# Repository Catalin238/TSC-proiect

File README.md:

# TSC-proiect

1. Diagrama Bloc

2. Bill of materials

| Piece Name | Quantity | Link |
|------------|----------|------|
| ESP32 | 1 | https://www.snapeda.com/parts/ESP32-C6-WROOM-1-N8/Espressif%20Systems/view-part/?ref=search&t=ESP32-C6-WROOM-1-N8 |
| BME680 | 1 | https://www.snapeda.com/parts/BME680/Bosch%20Sensortec/view-part/?ref=search&t=bme680 |
| DS3231SN | 1 | https://www.snapeda.com/parts/DS3231SN%23/Analog%20Devices/view-part/?ref=search&t=DS3231SN%23 |
| W25Q512JVEIQ | 1 | https://www.snapeda.com/parts/W25Q512JVEIQ/Winbond%20Electronics/view-part/?ref=search&t=W25Q512JVEIQ |
| MCP73831 | 1 | https://componentsearchengine.com/part-view/MCP73831T-2ACI%2FOT/Microchip |
| MOSFET | 1 | https://componentsearchengine.com/part-view/DMG2305UX-7/Diodes%20Incorporated |
| SAMACSYS_PARTS_USB4110-GF-A | 1 | https://www.snapeda.com/parts/USB4110-GF-A./Global%20Connector%20Technology/view-part/ |
| USBLC6-2SC6Y | 1 | https://www.snapeda.com/parts/USBLC6-2SC6Y/STMicroelectronics/view-part/?ref=dk&t=USBLC6-2SC6Y&con_ref=None |
| BD5229G-TR | 1 | https://www.snapeda.com/parts/BD5229G-TR/Rohm/view-part/?ref=search&t=BD5229G-TR |
| QWIIC_CONNECTOR | 1 | https://www.snapeda.com/parts/PRT-14417/SparkFun/view-part/ |
| CPH3225A | 1 | https://www.snapeda.com/parts/CPH3225A/Seiko/view-part/ |
| BUTTON_CUSYOMV1 | 3 | https://www.snapeda.com/search/?q=EVQP7L01P&search-type=parts |
| ADAFRUIT_LEDCHIP-LED0603 | 1 | https://www.snapeda.com/parts/KP-1608SURCK/Kingbright/view-part/?ref=search&t=LED%200603 |
| C0402 | 1 | https://componentsearchengine.com/part-view/CC0402MRX5R5BB106/YAGEO |
| 112ATAARR03 | 1 | https://www.snapeda.com/parts/112A-TAAR-R03/Attend/view-part/ |
| 744043680 | 1 | https://eu.mouser.com/ProductDetail/Wurth-Elektronik/744043680?qs=PGXP4M47uW6VkZq%252BkzjrHA%3D%3D |
| R0402 | 1 | https://componentsearchengine.com/part-view/R0402%201%25%20100%20K%20(RC0402FR-07100KL)/YAGEO |
| SD0805S020S1R0 | 1 | https://componentsearchengine.com/part-view/SD0805S020S1R0/Kyocera%20AVX |
| VARISTOR | 1 | https://ro.mouser.com/ProductDetail/EPCOS-TDK/B72520T0350K062?qs=dEfas%2FXlABIszF52uu7vrg%3D%3D |
| SRJ | 1 | https://componentsearchengine.com/part-view/FH34SRJ-24S-0.5SH(99)/Hirose |
| MBR0530 | 1 | https://www.snapeda.com/parts/MBR0530/Onsemi/view-part/ |
| PGB1010603MR | 1 | https://www.snapeda.com/parts/PGB1010603MR/Littelfuse/view-part/ |
| RCL_CPOL-EU | 1 | https://grabcad.com/library/tantalum-smd-capacitor-type-b-3528-1 |
| SI1308EDL-T1-GE3 | 1 | https://www.snapeda.com/parts/SI1308EDL-T1-GE3/Vishay/view-part/ |
| XC6220A331MR-G | 1 | https://ro.mouser.com/ProductDetail/Torex-Semiconductor/XC6220A331MR-G?qs=AsjdqWjXhJ8ZSWznL1J0gg%3D%3D&utm_source=octopart&utm_medium=aggregator&utm_campaign=865-XC6220A331MR-G&utm_content=Torex%20Semiconductor |

3. Functionalitati Hardware

Structura si Functionalitati:

ESP32-C6-WROOM-1-N8
Functie: Procesor central al sistemului, gestioneaza protocoalele de comunicare (SPI, I2C, UART), achizitia datelor de la senzori si controlul dispozitivelor periferice.

Connector USB-C cu Protectie ESD
Functie: Ofera posibilitatea incarcarii prin port USB-C si implementeaza circuite de protectie impotriva descarcarilor electrostatice.

Controller de Incarcare (MCP73831)
Functie: Administreaza procesul de incarcare pentru acumulatorul Li-Po si regleaza parametrii curentului de incarcare.

Acumulator Li-Po
Functie: Furnizeaza energie autonoma, permitand functionarea dispozitivului independent de conexiunea USB.

Regulator de Tensiune LDO
Functie: Converteste si mentine o tensiune stabila de 3.3V pentru alimentarea microcontrolerului si a componentelor auxiliare.

Memorie Flash NOR Externa 64MB
Functie: Asigura spatiu de stocare aditional pentru date operationale si actualizari de firmware.

Modul RTC (DS3231SN)
Functie: Asigura cronometrarea precisa si mentinerea datei/orei curente.
Conectivitate: Protocol I2C, include functii de alarma si baterie de rezerva pentru mentinerea timpului.

Senzor de Mediu (BME688)
Functie: Colecteaza parametri ambientali precum temperatura, umiditatea, presiunea atmosferica si compusi organici volatili.
Conectivitate: Comunicare I2C, optimizat pentru consum redus in standby, cu capacitati avansate de detectare a gazelor.
Implementare: Utilizeaza interfata standardizata Qwiic / Stemma QT pentru conectare plug-and-play.

Circuit de Control pentru Afisaj E-Paper si Conector
Functie: Produce semnalele specifice pentru operarea afisajelor electroforetice si faciliteaza compatibilitatea cu diferite tipuri de ecrane.
Conectivitate: Protocol SPI, cu linii dedicate pentru control (Busy, Reset, DC, CS).

Card SD
Functie: Faciliteaza stocarea extinsa a datelor, fisierelor de configurare si inregistrarilor pe termen lung.
Conectivitate: Interfata SPI cu linie dedicata de selectie.

Supervisor de Tensiune si Butoane Reset/Boot
Functie: Supravegheaza nivelul tensiunii de alimentare si controleaza secventele de initializare si repornire ale ESP32-C6.

Interfete si Protocoale de Comunicare:

I2C: Implementat pentru comunicarea cu BME688 si DS3231SN.
SPI: Utilizat pentru accesarea memoriei Flash NOR, controlul afisajului E-Paper si operatiunile cu cardul SD.
UART: Disponibil pentru debugging si integrarea modulelor externe optionale.
Wi-Fi si Bluetooth LE: Functionalitati native ale ESP32-C6.

Analiza Consumului Energetic:

ESP32-C6:
Consum in regim activ: ~80-240 mA (variabil in functie de activitatea Wi-Fi/BT).
Consum in regim economic: sub 1 mA (in modul deep sleep).

BME688:
Consum caracteristic: ~2.1 µA in repaus, maxim ~3.1 mA in operare completa.

Memorie Flash NOR:
Consum la citire/scriere: 5-15 mA, in asteptare: sub 10 µA.

DS3231SN:
Consum constant: aproximativ 150 µA cu functia de backup activa.

Regulator LDO:
Randamentul energetic variaza in functie de diferenta dintre tensiunea de intrare si cea de iesire (3.3V) si de curentul total solicitat.

4. Pini ESP32-C6

| Pin ESP32-C6  | Componenta / Rol                       | Descriere                             |
|---------------|---------------------------------------|---------------------------------------|
| IO8 (SCK)     | SPI Clock                             | Semnal de clock SPI                   |
| IO6 (MOSI)    | SPI MOSI catre NOR Flash, E-Paper, SD Card | Transfer date catre periferice SPI   |
| IO7 (MISO)    | SPI MISO din NOR Flash, E-Paper, SD Card | Receptie date de la periferice SPI |
| IO9 (CS1)     | Chip Select NOR Flash                 | Control dedicat pentru NOR Flash      |
| IO11 (CS3)    | Chip Select SD Card                   | Control dedicat pentru SD Card        |
| IO10 (CS2)    | Chip Select E-Paper Display           | Control dedicat pentru Display        |
| IO15 (SCL)    | I2C SCL catre BME688 si DS3231SN      | Semnal de clock I2C                   |
| IO14 (SDA)    | I2C SDA catre BME688 si DS3231SN      | Date pentru I2C         |
| IO21          | Reset/Boot control                    | Butoane de reset si boot              |
| IO16, IO17    | UART RX, TX (debug)                   | Debug serial si configurare           |

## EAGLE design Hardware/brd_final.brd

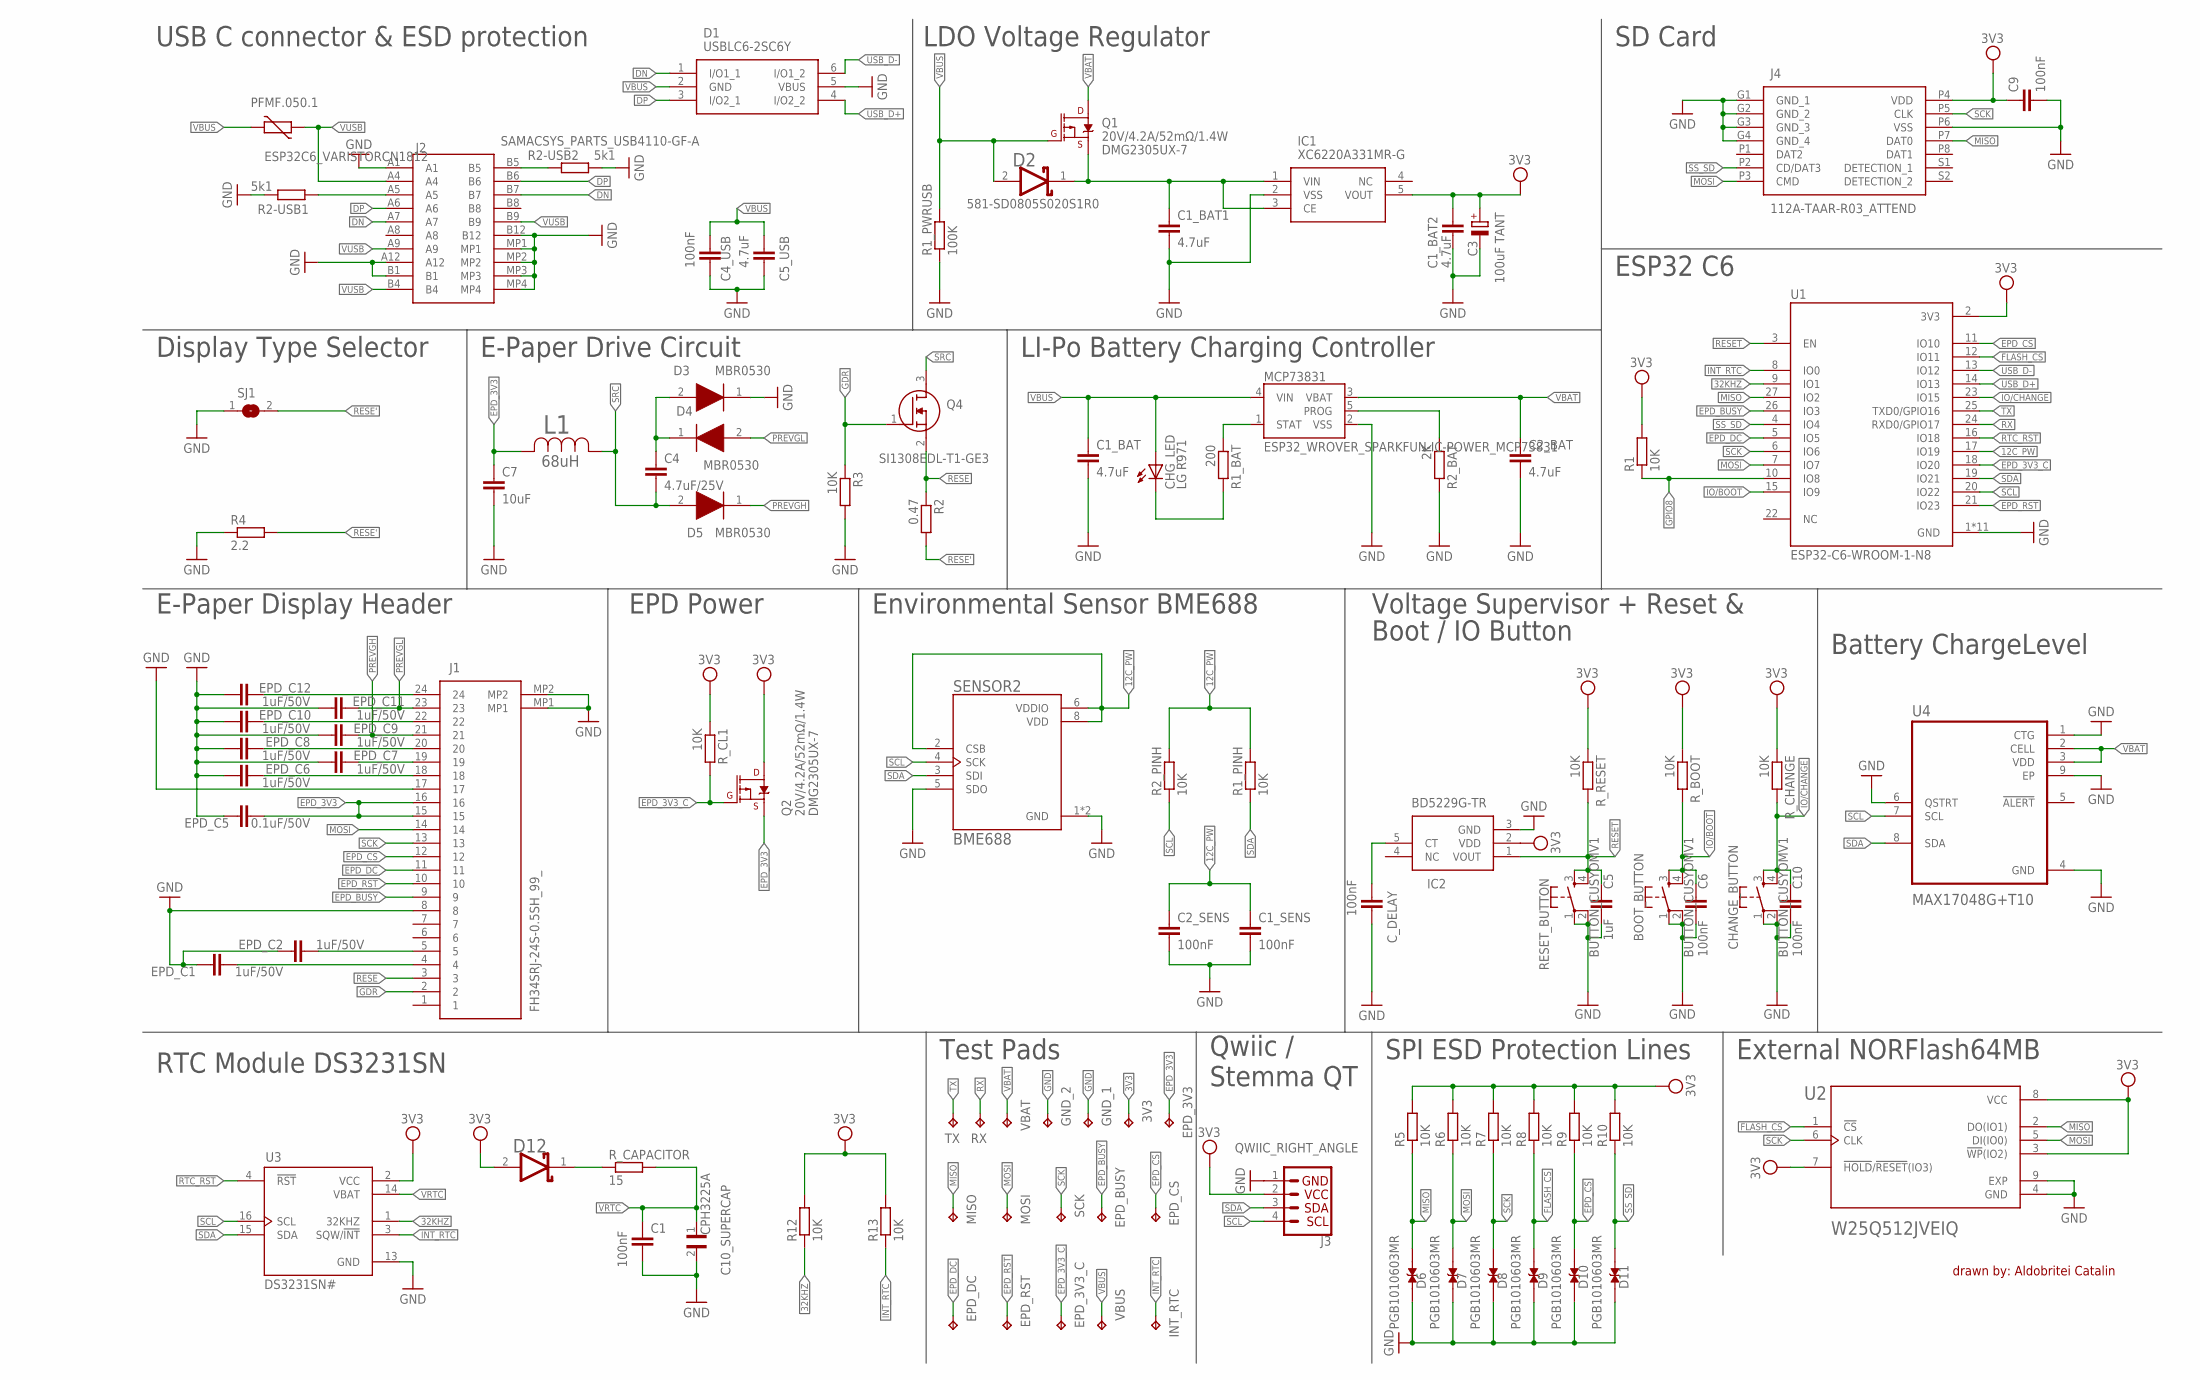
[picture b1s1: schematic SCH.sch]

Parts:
3V3: TPTP20R; TP20R
BOOT_BUTTON: BUTTON_CUSYOMV1; MYBUTTON
C1, C1_SENS, C2_SENS, C4_USB, C6, C9, C10: 100nF; EAGLE-LTSPICE_C0402
C1_BAT, C1_BAT1, C1_BAT2, C2_BAT, C5_USB: 4.7uF; EAGLE-LTSPICE_C0402
C3: 100uF TANT; RCL_CT3528
C4: 4.7uF/25V; EAGLE-LTSPICE_C0402
C5: 1uF; EAGLE-LTSPICE_C0402
C7: 10uF; EAGLE-LTSPICE_C0402
C10_SUPERCAP: CPH3225A; CAPCP3225X100N
CHANGE_BUTTON: BUTTON_CUSYOMV1; MYBUTTON
CHG_LED: LG R971; ADAFRUIT_CHIP-LED0603
C_DELAY: 100nF; EAGLE-LTSPICE_C0402
D1: USBLC6-2SC6Y; SOT95P280X145-6N
D2, D12: ESP32_WROVER_AVX---SD0805S020S1R0_AVX_SD0805S020S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; ESP32_WROVER_AVX---SD0805S020S1R0_AVX_SD0805S020S1R0_0
D3, D4, D5: MBR0530; SOD3716X135N
D6, D7, D8, D9, D10, D11: PGB1010603MR; DIOC1608X36N
EPD_3V3, EPD_3V3_C: TPTP20R; TP20R
EPD_BUSY: TPTP20R; TP20R
EPD_C1, EPD_C2, EPD_C6, EPD_C7, EPD_C8, EPD_C9, EPD_C10, EPD_C11, EPD_C12: 1uF/50V; EAGLE-LTSPICE_C0402
EPD_C5: 0.1uF/50V; EAGLE-LTSPICE_C0402
EPD_CS: TPTP20R; TP20R
EPD_DC: TPTP20R; TP20R
EPD_RST: TPTP20R; TP20R
GND_1, GND_2: TPTP20R; TP20R
IC1: XC6220A331MR-G; SOT95P280X120-5N
IC2: BD5229G-TR; SOT95P280X125-5N
INT_RTC: TPTP20R; TP20R
J1: FH34SRJ-24S-0.5SH_99_; FH34SRJ24S05SH99
J2: SAMACSYS_PARTS_USB4110-GF-A; SAMACSYS_PARTS_USB4110GFA
J3: QWIIC_RIGHT_ANGLE; JST04_1MM_RA
J4: 112A-TAAR-R03_ATTEND; 112ATAARR03ATTEND
L1: 68uH; IND_4828-WE-TPC_WRE
MCP73831: ESP32_WROVER_SPARKFUN-IC-POWER_MCP73831; ESP32_WROVER_SPARKFUN-IC-POWER_SOT23-5
MISO: TPTP20R; TP20R
MOSI: TPTP20R; TP20R
PFMF.050.1: ESP32C6_VARISTORCN1812; ESP32C6_VARISTOR_CT/CN1812
Q1, Q2: 20V/4.2A/52mΩ/1.4W; ESP32_WROVER_SPARKFUN-DISCRETESEMI_SOT23-3
Q4: SI1308EDL-T1-GE3; SOT65P210X110-3N
R1, R1_PINH, R2_PINH, R3, R5, R6, R7, R8, R9, R10, R12, R13: 10K; ESP32_WROVER_EAGLE-LTSPICE_R0402
R1_BAT: 200; ESP32_WROVER_EAGLE-LTSPICE_R0402
R1_PWRUSB: 100K; ESP32_WROVER_EAGLE-LTSPICE_R0402
R2: 0.47; ESP32_WROVER_EAGLE-LTSPICE_R0402
R2-USB1, R2-USB2: 5k1; ESP32_WROVER_EAGLE-LTSPICE_R0402
R2_BAT: 2K; ESP32_WROVER_EAGLE-LTSPICE_R0402
R4: 2.2; ESP32_WROVER_EAGLE-LTSPICE_R0402
RESET_BUTTON: BUTTON_CUSYOMV1; MYBUTTON
RX: TPTP20R; TP20R
R_BOOT: 10K; ESP32_WROVER_EAGLE-LTSPICE_R0402
R_CAPACITOR: 15; ESP32_WROVER_EAGLE-LTSPICE_R0402
R_CHANGE: 10K; ESP32_WROVER_EAGLE-LTSPICE_R0402
R_CL1: 10K; ESP32_WROVER_EAGLE-LTSPICE_R0402
R_RESET: 10K; ESP32_WROVER_EAGLE-LTSPICE_R0402
SCK: TPTP20R; TP20R
SENSOR2: BME688; ESP32_WROVER_BME680_PSON80P300X300X100-8N
SJ1: SJ
TX: TPTP20R; TP20R
U1: ESP32-C6-WROOM-1-N8; XCVR_ESP32-C6-WROOM-1-N8
U2: W25Q512JVEIQ; SON127P600X800X80-9N
U3: DS3231SN#; SOIC127P1032X265-16N
U4: MAX17048G+T10; SON50P200X200X80-9N
VBAT: TPTP20R; TP20R
VBUS: TPTP20R; TP20R

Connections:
3V3: 3V3.TP, C1_BAT2.2, C3.+, C9.1, D12.2 (ANODE), IC1.5 (VOUT), IC2.2 (VDD), J3.2, J4.P4 (VDD), Q2.3 (D), R1.2, R5.2, R6.2, R7.2, R8.2, R9.2, R10.2, R12.2, R13.2, R_BOOT.1, R_CHANGE.1, R_CL1.1, R_RESET.1, U1.2 (3V3), U2.3 (!WP!(IO2)), U2.7 (!HOLD!/!RESET!(IO3)), U2.8 (VCC), U3.2 (VCC)
32KHZ: R12.1, U1.9 (IO1), U3.1 (32KHZ)
DN: D1.1 (I/O1_1), J2.A7, J2.B7
DP: D1.3 (I/O2_1), J2.A6, J2.B6
EPD_3V3: C7.1, EPD_3V3.TP, EPD_C5.2, J1.15, J1.16, L1.2, Q2.2 (S)
EPD_3V3_C: EPD_3V3_C.TP, Q2.1 (G), R_CL1.2, U1.18 (IO20)
EPD_BUSY: EPD_BUSY.TP, J1.9, U1.26 (IO3)
EPD_CS: D10.2, EPD_CS.TP, J1.12, R9.1, U1.11 (IO10)
EPD_DC: EPD_DC.TP, J1.11, U1.5 (IO5)
EPD_RST: EPD_RST.TP, J1.10, U1.21 (IO23)
FLASH_CS: D9.2, R8.1, U1.12 (IO11), U2.1 (!CS)
GDR: J1.2, Q4.1 (G), R3.1
GND: BOOT_BUTTON.1, BOOT_BUTTON.2, C1.2, C1_BAT.2, C1_BAT1.2, C1_BAT2.1, C1_SENS.2, C2_BAT.2, C2_SENS.2, C3.-, C4_USB.2, C5.2, C5_USB.2, C6.2, C7.2, C9.2, C10.2, C10_SUPERCAP.2, CHANGE_BUTTON.1, CHANGE_BUTTON.2, C_DELAY.2, D1.5 (VBUS), D3.1 (K), D6.1, D7.1, D8.1, D9.1, D10.1, D11.1, EPD_C1.1, EPD_C2.1, EPD_C5.1, EPD_C6.1, EPD_C7.1, EPD_C8.1, EPD_C9.1, EPD_C10.1, EPD_C11.1, EPD_C12.1, GND_1.TP, GND_2.TP, IC1.2 (VSS), IC2.3 (GND), J1.8, J1.17, J1.MP1, J1.MP2, J2.A1, J2.A12, J2.B1, J2.B12, J2.MP1, J2.MP2, J2.MP3, J2.MP4, J3.1, J4.G1 (GND_1), J4.G2 (GND_2), J4.G3 (GND_3), J4.G4 (GND_4), J4.P6 (VSS), MCP73831.2 (VSS), R1_PWRUSB.1, R2-USB1.1, R2-USB2.2, R2_BAT.2, R3.2, R4.1, RESET_BUTTON.1, RESET_BUTTON.2, SENSOR2.1 (GND), SENSOR2.5 (SDO), SENSOR2.7 (GND), SJ1.1, U1.1 (GND), U1.28 (GND), U1.29_1 (GND), U1.29_2 (GND), U1.29_3 (GND), U1.29_4 (GND), U1.29_5 (GND), U1.29_6 (GND), U1.29_7 (GND), U1.29_8 (GND), U1.29_9 (GND), U2.4 (GND), U2.9 (EXP), U3.13 (GND), U4.1 (CTG), U4.4 (GND), U4.6 (QSTRT), U4.9 (EP)
GND1: J2.B5, R2-USB2.1
GPIO8: R1.1, U1.10 (IO8)
INT_RTC: INT_RTC.TP, R13.1, U1.8 (IO0), U3.3 (SQW/!INT)
IO/BOOT: BOOT_BUTTON.3, BOOT_BUTTON.4, C6.1, R_BOOT.2, U1.15 (IO9)
IO/CHANGE: C10.1, CHANGE_BUTTON.3, CHANGE_BUTTON.4, R_CHANGE.2, U1.23 (IO15)
MISO: D6.2, J4.P7 (DAT0), MISO.TP, R5.1, U1.27 (IO2), U2.2 (DO(IO1))
MOSI: D7.2, J1.14, J4.P3 (CMD), MOSI.TP, R6.1, U1.7 (IO7), U2.5 (DI(IO0))
unnamed: J2.A5, R2-USB1.2
unnamed: EPD_C7.2, J1.19
unnamed: MCP73831.1 (STAT), R1_BAT.1
unnamed: C1_BAT1.1, D2.1 (CATHODE), IC1.1 (VIN), IC1.3 (CE), Q1.2 (S)
unnamed: CHG_LED.C, R1_BAT.2
unnamed: EPD_C6.2, J1.18
unnamed: MCP73831.5 (PROG), R2_BAT.1
unnamed: C4.1, D3.2 (A), D4.1 (K)
unnamed: EPD_C8.2, J1.20
unnamed: EPD_C10.2, J1.22
unnamed: EPD_C12.2, J1.24
unnamed: C_DELAY.1, IC2.5 (CT)
unnamed: EPD_C2.2, J1.5
unnamed: EPD_C1.2, J1.4
unnamed: D12.1 (CATHODE), R_CAPACITOR.1
PREVGH: D5.1 (K), EPD_C9.2, J1.21
PREVGL: D4.2 (A), EPD_C11.2, J1.23
RESE: J1.3, Q4.2 (S), R2.1
RESE': R2.2, R4.2, SJ1.2
RESET: C5.1, IC2.1 (VOUT), RESET_BUTTON.3, RESET_BUTTON.4, R_RESET.2, U1.3 (EN)
RTC_RST: U1.16 (IO18), U3.4 (!RST)
RX: RX.TP, U1.24 (RXD0/GPIO17)
SCK: D8.2, J1.13, J4.P5 (CLK), R7.1, SCK.TP, U1.6 (IO6), U2.6 (CLK)
SCL: J3.4, R2_PINH.1, SENSOR2.4 (SCK), U1.20 (IO22), U3.16 (SCL), U4.7 (SCL)
SDA: J3.3, R1_PINH.1, SENSOR2.3 (SDI), U1.19 (IO21), U3.15 (SDA), U4.8 (SDA)
SRC: C4.2, D5.2 (A), L1.1, Q4.3 (D)
SS_SD: D11.2, J4.P2 (CD/DAT3), R10.1, U1.4 (IO4)
TX: TX.TP, U1.25 (TXD0/GPIO16)
USB_D+: D1.4 (I/O2_2), U1.14 (IO13)
USB_D-: D1.6 (I/O1_2), U1.13 (IO12)
VBAT: C2_BAT.1, MCP73831.3 (VBAT), Q1.3 (D), U4.2 (CELL), U4.3 (VDD), VBAT.TP
VBUS: C1_BAT.1, C4_USB.1, C5_USB.1, CHG_LED.A, D1.2 (GND), D2.2 (ANODE), MCP73831.4 (VIN), PFMF.050.1.2, Q1.1 (G), R1_PWRUSB.2, VBUS.TP
VRTC: C1.1, C10_SUPERCAP.1, R_CAPACITOR.2, U3.14 (VBAT)
VUSB: J2.A4, J2.A9, J2.B4, J2.B9, PFMF.050.1.1

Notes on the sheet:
USB C connector & ESD protection
LDO Voltage Regulator
SD Card
ESP32 C6
LI-Po Battery Charging Controller
E-Paper Drive Circuit
Display Type Selector
E-Paper Display Header
EPD Power
Environmental Sensor BME688
Voltage Supervisor + Reset &
Boot / IO Button
Battery ChargeLevel
RTC Module DS3231SN
Test Pads
Qwiic / Stemma QT
SPI ESD Protection Lines
External NORFlash64MB
drawn by: Aldobritei Catalin

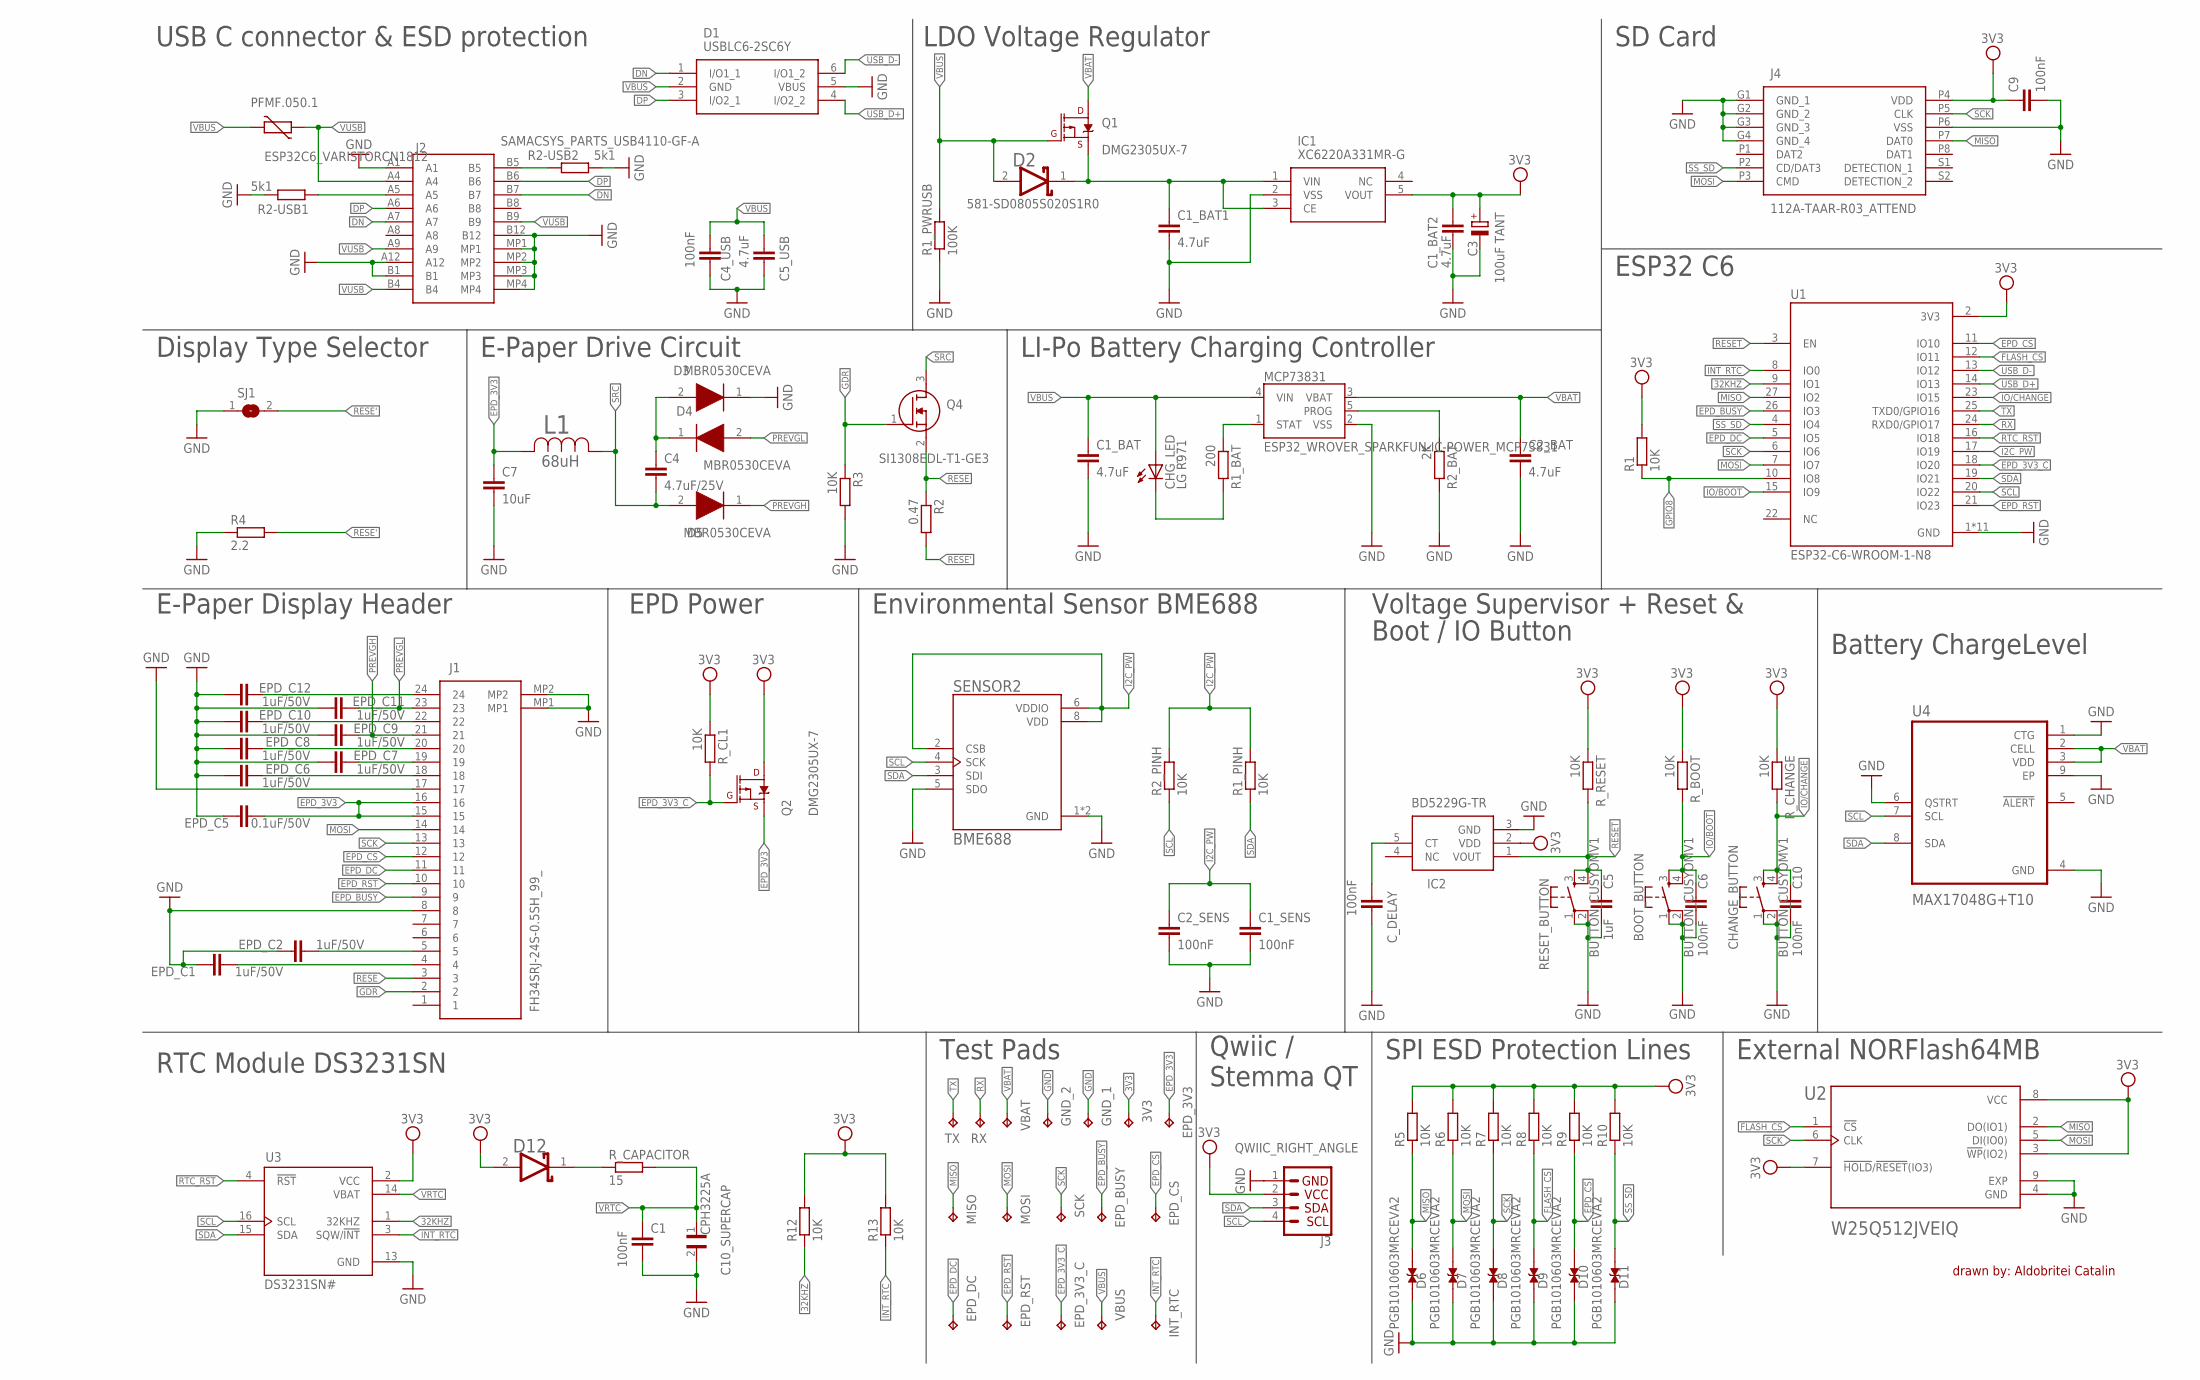
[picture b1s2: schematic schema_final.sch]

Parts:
3V3: TP; TP20R
BOOT_BUTTON: BUTTON_CUSYOMV1; MYBUTTON
C1, C1_SENS, C2_SENS, C4_USB, C6, C9, C10: 100nF; EAGLE-LTSPICE_C0402
C1_BAT, C1_BAT1, C1_BAT2, C2_BAT, C5_USB: 4.7uF; EAGLE-LTSPICE_C0402
C3: 100uF TANT; RCL_CT3528
C4: 4.7uF/25V; EAGLE-LTSPICE_C0402
C5: 1uF; EAGLE-LTSPICE_C0402
C7: 10uF; EAGLE-LTSPICE_C0402
C10_SUPERCAP: CPH3225A; CAPCP3225X100N
CHANGE_BUTTON: BUTTON_CUSYOMV1; MYBUTTON
CHG_LED: LG R971; ADAFRUIT_CHIP-LED0603
C_DELAY: 100nF; EAGLE-LTSPICE_C0402
D1: USBLC6-2SC6Y; SOT95P280X145-6N
D2, D12: ESP32_WROVER_AVX---SD0805S020S1R0_AVX_SD0805S020S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; ESP32_WROVER_AVX---SD0805S020S1R0_AVX_SD0805S020S1R0_0
D3, D4, D5: MBR0530CEVA; SOD3716X135N
D6, D7, D8, D9, D10, D11: PGB1010603MRCEVA2; DIOC1608X36N
EPD_3V3, EPD_3V3_C: TP; TP20R
EPD_BUSY: TP; TP20R
EPD_C1, EPD_C2, EPD_C6, EPD_C7, EPD_C8, EPD_C9, EPD_C10, EPD_C11, EPD_C12: 1uF/50V; EAGLE-LTSPICE_C0402
EPD_C5: 0.1uF/50V; EAGLE-LTSPICE_C0402
EPD_CS: TP; TP20R
EPD_DC: TP; TP20R
EPD_RST: TP; TP20R
GND_1, GND_2: TP; TP20R
IC1: XC6220A331MR-G; SOT95P280X120-5N
IC2: BD5229G-TR; SOT95P280X125-5N
INT_RTC: TP; TP20R
J1: FH34SRJ-24S-0.5SH_99_; FH34SRJ24S05SH99
J2: SAMACSYS_PARTS_USB4110-GF-A; SAMACSYS_PARTS_USB4110GFA
J3: QWIIC_RIGHT_ANGLE; JST04_1MM_RA
J4: 112A-TAAR-R03_ATTEND; 112ATAARR03ATTEND
L1: 68uH; IND_4828-WE-TPC_WRE
MCP73831: ESP32_WROVER_SPARKFUN-IC-POWER_MCP73831; ESP32_WROVER_SPARKFUN-IC-POWER_SOT23-5
MISO: TP; TP20R
MOSI: TP; TP20R
PFMF.050.1: ESP32C6_VARISTORCN1812; ESP32C6_VARISTOR_CT/CN1812
Q1, Q2: 20V/4.2A/52mΩ/1.4W; ESP32_WROVER_SPARKFUN-DISCRETESEMI_SOT23-3
Q4: SI1308EDL-T1-GE3; SOT65P210X110-3N
R1, R1_PINH, R2_PINH, R3, R5, R6, R7, R8, R9, R10, R12, R13: 10K; ESP32_WROVER_EAGLE-LTSPICE_R0402
R1_BAT: 200; ESP32_WROVER_EAGLE-LTSPICE_R0402
R1_PWRUSB: 100K; ESP32_WROVER_EAGLE-LTSPICE_R0402
R2: 0.47; ESP32_WROVER_EAGLE-LTSPICE_R0402
R2-USB1, R2-USB2: 5k1; ESP32_WROVER_EAGLE-LTSPICE_R0402
R2_BAT: 2K; ESP32_WROVER_EAGLE-LTSPICE_R0402
R4: 2.2; ESP32_WROVER_EAGLE-LTSPICE_R0402
RESET_BUTTON: BUTTON_CUSYOMV1; MYBUTTON
RX: TP; TP20R
R_BOOT: 10K; ESP32_WROVER_EAGLE-LTSPICE_R0402
R_CAPACITOR: 15; ESP32_WROVER_EAGLE-LTSPICE_R0402
R_CHANGE: 10K; ESP32_WROVER_EAGLE-LTSPICE_R0402
R_CL1: 10K; ESP32_WROVER_EAGLE-LTSPICE_R0402
R_RESET: 10K; ESP32_WROVER_EAGLE-LTSPICE_R0402
SCK: TP; TP20R
SENSOR2: BME688; ESP32_WROVER_BME680_PSON80P300X300X100-8N
SJ1: SJ
TX: TP; TP20R
U1: ESP32-C6-WROOM-1-N8; XCVR_ESP32-C6-WROOM-1-N8
U2: W25Q512JVEIQ; SON127P600X800X80-9N
U3: DS3231SN#; SOIC127P1032X265-16N
U4: MAX17048G+T10; SON50P200X200X80-9N
VBAT: TP; TP20R
VBUS: TP; TP20R

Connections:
3V3: 3V3.TP, C1_BAT2.2, C3.+, C9.1, D12.2 (ANODE), IC1.5 (VOUT), IC2.2 (VDD), J3.2, J4.P4 (VDD), Q2.3 (D), R1.2, R5.2, R6.2, R7.2, R8.2, R9.2, R10.2, R12.2, R13.2, R_BOOT.1, R_CHANGE.1, R_CL1.1, R_RESET.1, U1.2 (3V3), U2.3 (!WP!(IO2)), U2.7 (!HOLD!/!RESET!(IO3)), U2.8 (VCC), U3.2 (VCC)
32KHZ: R12.1, U1.9 (IO1), U3.1 (32KHZ)
DN: D1.1 (I/O1_1), J2.A7, J2.B7
DP: D1.3 (I/O2_1), J2.A6, J2.B6
EPD_3V3: C7.1, EPD_3V3.TP, EPD_C5.2, J1.15, J1.16, L1.2, Q2.2 (S)
EPD_3V3_C: EPD_3V3_C.TP, Q2.1 (G), R_CL1.2, U1.18 (IO20)
EPD_BUSY: EPD_BUSY.TP, J1.9, U1.26 (IO3)
EPD_CS: D10.2, EPD_CS.TP, J1.12, R9.1, U1.11 (IO10)
EPD_DC: EPD_DC.TP, J1.11, U1.5 (IO5)
EPD_RST: EPD_RST.TP, J1.10, U1.21 (IO23)
FLASH_CS: D9.2, R8.1, U1.12 (IO11), U2.1 (!CS)
GDR: J1.2, Q4.1 (G), R3.1
GND: BOOT_BUTTON.1, BOOT_BUTTON.2, C1.2, C1_BAT.2, C1_BAT1.2, C1_BAT2.1, C1_SENS.2, C2_BAT.2, C2_SENS.2, C3.-, C4_USB.2, C5.2, C5_USB.2, C6.2, C7.2, C9.2, C10.2, C10_SUPERCAP.2, CHANGE_BUTTON.1, CHANGE_BUTTON.2, C_DELAY.2, D1.5 (VBUS), D3.1 (K), D6.1, D7.1, D8.1, D9.1, D10.1, D11.1, EPD_C1.1, EPD_C2.1, EPD_C5.1, EPD_C6.1, EPD_C7.1, EPD_C8.1, EPD_C9.1, EPD_C10.1, EPD_C11.1, EPD_C12.1, GND_1.TP, GND_2.TP, IC1.2 (VSS), IC2.3 (GND), J1.8, J1.17, J1.MP1, J1.MP2, J2.A1, J2.A12, J2.B1, J2.B12, J2.MP1, J2.MP2, J2.MP3, J2.MP4, J3.1, J4.G1 (GND_1), J4.G2 (GND_2), J4.G3 (GND_3), J4.G4 (GND_4), J4.P6 (VSS), MCP73831.2 (VSS), R1_PWRUSB.1, R2-USB1.1, R2-USB2.2, R2_BAT.2, R3.2, R4.1, RESET_BUTTON.1, RESET_BUTTON.2, SENSOR2.1 (GND), SENSOR2.5 (SDO), SENSOR2.7 (GND), SJ1.1, U1.1 (GND), U1.28 (GND), U1.29_1 (GND), U1.29_2 (GND), U1.29_3 (GND), U1.29_4 (GND), U1.29_5 (GND), U1.29_6 (GND), U1.29_7 (GND), U1.29_8 (GND), U1.29_9 (GND), U2.4 (GND), U2.9 (EXP), U3.13 (GND), U4.1 (CTG), U4.4 (GND), U4.6 (QSTRT), U4.9 (EP)
GND1: J2.B5, R2-USB2.1
GPIO8: R1.1, U1.10 (IO8)
INT_RTC: INT_RTC.TP, R13.1, U1.8 (IO0), U3.3 (SQW/!INT)
IO/BOOT: BOOT_BUTTON.3, BOOT_BUTTON.4, C6.1, R_BOOT.2, U1.15 (IO9)
IO/CHANGE: C10.1, CHANGE_BUTTON.3, CHANGE_BUTTON.4, R_CHANGE.2, U1.23 (IO15)
MISO: D6.2, J4.P7 (DAT0), MISO.TP, R5.1, U1.27 (IO2), U2.2 (DO(IO1))
MOSI: D7.2, J1.14, J4.P3 (CMD), MOSI.TP, R6.1, U1.7 (IO7), U2.5 (DI(IO0))
unnamed: J2.A5, R2-USB1.2
unnamed: EPD_C7.2, J1.19
unnamed: MCP73831.1 (STAT), R1_BAT.1
unnamed: C1_BAT1.1, D2.1 (CATHODE), IC1.1 (VIN), IC1.3 (CE), Q1.2 (S)
unnamed: CHG_LED.C, R1_BAT.2
unnamed: EPD_C6.2, J1.18
unnamed: MCP73831.5 (PROG), R2_BAT.1
unnamed: C4.1, D3.2 (A), D4.1 (K)
unnamed: EPD_C8.2, J1.20
unnamed: EPD_C10.2, J1.22
unnamed: EPD_C12.2, J1.24
unnamed: C_DELAY.1, IC2.5 (CT)
unnamed: EPD_C2.2, J1.5
unnamed: EPD_C1.2, J1.4
unnamed: D12.1 (CATHODE), R_CAPACITOR.1
PREVGH: D5.1 (K), EPD_C9.2, J1.21
PREVGL: D4.2 (A), EPD_C11.2, J1.23
RESE: J1.3, Q4.2 (S), R2.1
RESE': R2.2, R4.2, SJ1.2
RESET: C5.1, IC2.1 (VOUT), RESET_BUTTON.3, RESET_BUTTON.4, R_RESET.2, U1.3 (EN)
RTC_RST: U1.16 (IO18), U3.4 (!RST)
RX: RX.TP, U1.24 (RXD0/GPIO17)
SCK: D8.2, J1.13, J4.P5 (CLK), R7.1, SCK.TP, U1.6 (IO6), U2.6 (CLK)
SCL: J3.4, R2_PINH.1, SENSOR2.4 (SCK), U1.20 (IO22), U3.16 (SCL), U4.7 (SCL)
SDA: J3.3, R1_PINH.1, SENSOR2.3 (SDI), U1.19 (IO21), U3.15 (SDA), U4.8 (SDA)
SRC: C4.2, D5.2 (A), L1.1, Q4.3 (D)
SS_SD: D11.2, J4.P2 (CD/DAT3), R10.1, U1.4 (IO4)
TX: TX.TP, U1.25 (TXD0/GPIO16)
USB_D+: D1.4 (I/O2_2), U1.14 (IO13)
USB_D-: D1.6 (I/O1_2), U1.13 (IO12)
VBAT: C2_BAT.1, MCP73831.3 (VBAT), Q1.3 (D), U4.2 (CELL), U4.3 (VDD), VBAT.TP
VBUS: C1_BAT.1, C4_USB.1, C5_USB.1, CHG_LED.A, D1.2 (GND), D2.2 (ANODE), MCP73831.4 (VIN), PFMF.050.1.2, Q1.1 (G), R1_PWRUSB.2, VBUS.TP
VRTC: C1.1, C10_SUPERCAP.1, R_CAPACITOR.2, U3.14 (VBAT)
VUSB: J2.A4, J2.A9, J2.B4, J2.B9, PFMF.050.1.1

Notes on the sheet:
USB C connector & ESD protection
LDO Voltage Regulator
SD Card
ESP32 C6
LI-Po Battery Charging Controller
E-Paper Drive Circuit
Display Type Selector
E-Paper Display Header
EPD Power
Environmental Sensor BME688
Voltage Supervisor + Reset &
Boot / IO Button
Battery ChargeLevel
RTC Module DS3231SN
Test Pads
Qwiic / Stemma QT
SPI ESD Protection Lines
External NORFlash64MB
drawn by: Aldobritei Catalin

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
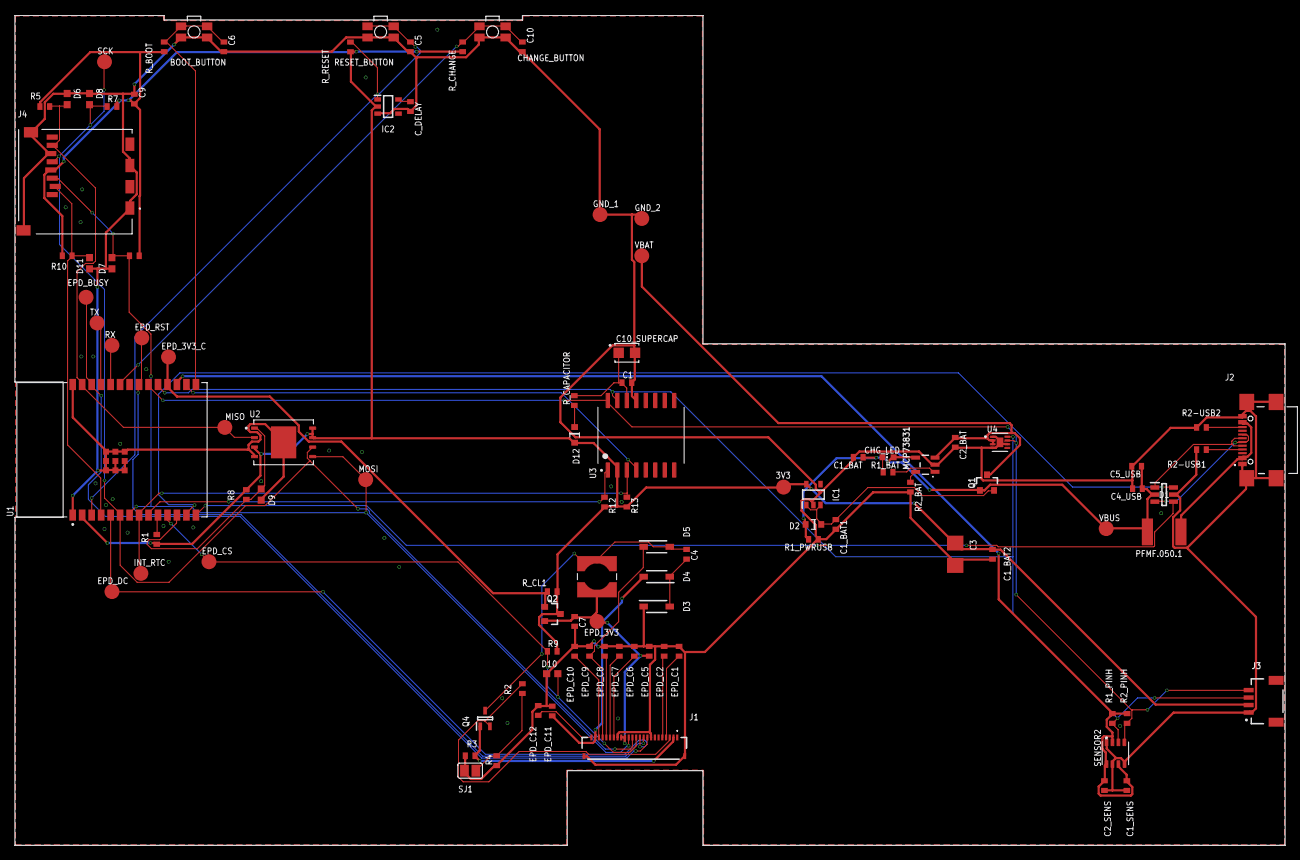
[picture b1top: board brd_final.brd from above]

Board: 2 copper layers, 170.2 x 111.2 mm, 103 parts (0 on the bottom side), 55 nets.

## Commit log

2025-04-16 final
    final

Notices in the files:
parts and their libraries:
DeskAssistant v19 v1: COPYRIGHT: Copyright (C) 2024 Ultra Librarian. All rights reserved.
